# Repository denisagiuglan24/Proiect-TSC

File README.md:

# Proiect TSC - InkTime Smartwatch
**Student:** Giuglan Denisa-Cristina  
**Grupa:** 334CD  
---

## 1. Viziunea Proiectului si Arhitectura Sistemului

### Diagrama Bloc Hardware
Am structurat conexiunile pentru a separa magistrala rapida SPI (display) de magistrala senzorilor I2C, asigurand astfel o integritate maxima a semnalului.

```text
       ALIMENTARE (POWER)             SISTEM CENTRAL (MCU)                INTERFETE I/O
    _____________________          ___________________________          ____________________
   |                     |        |                           |        |                    |
   |   USB-C Connector   |---5V---|      nRF52840 (SoC)       |--SPI-->|   DISPLAY E-PAPER  |
   |_____________________|        |    Cortex-M4F @ 64MHz     |   Bus  |   (1.54" 24-pin)   |
              |                   |___________________________|        |____________________|
              v                    | P0.02 (SCK) | P0.03 (MOSI)
    _____________________          | P0.15 (DC)  | P0.16 (RST)          ____________________
   |                     |        |___________________________|        |                    |
   |   BQ25180 Charger   |--VBAT--|      MAGISTRALA I2C       |<------>|   ACCEL. BMA421    |
   |  (Li-Po Management) |        |      (SDA / SCL)          |   Bus  |   MAX17048 GAUGE   |
   |_____________________|        |___________________________|        |   DRV2605 HAPTIC   |
              ^                    | P0.26 (SDA) | P0.27 (SCL)         |____________________|
              |                    |___________________________|
    __________|__________          |                           |        ____________________
   |                     |         |   GPIO / PWM CONTROL      |       |                    |
   |   BATERIE LI-PO     |         |                           |------>|   MOTOR VIBRATII   |
   |      250 mAh        |         | P1.11 (PWM) | P0.13 (UP)  |       |____________________|
   |_____________________|         | P0.14 (ENT) | P1.02 (DN)  |<------|    3x BUTOANE      |
              |                    |___________________________|       |____________________|
              v                              |
    _____________________          __________|__________                ____________________
   |                     |        |                     |              |                    |
   |   RT6160A BUCK-B    |--3.3V--|   CRISTAL EXTERN    |------------->|      ANTENA RF     |
   |  (System Power)     |        |    (32.768 kHz)     |              |     (2.4 GHz)      |
   |_____________________|        |_____________________|              |____________________|
```
## 2. Documentatia Componentelor (BOM)

Am selectat componentele bazandu-ma pe catalogul **JLC Parts**, urmarind un raport optim intre dimensiune si performanta. Toate piesele pasive (rezistente/condensatoare) sunt in capsule **0201** si **0402**.

| Componenta | Package | Cod JLC Parts | Datasheet |
|:---|:---|:---|:---|
| **nRF52840-QIAA-R** (MCU) | aQFN73 | [C190794](https://jlcpcb.com/partdetail/Nordic_Semicon-NRF52840_QIAA_R/C190794) | [Link](https://docs.nordicsemi.com/) |
| **E-Paper Display 1.54"** | 24-pin FPC | [C359944](https://jlcpcb.com/partdetail/Waveshare-4_2inch_e_PaperModule/C359944) | [Link](https://www.waveshare.com/w/upload/e/e6/1.54inch_e-Paper_Datasheet.pdf) |
| **BQ25180YBGR** (Charger) | DSBGA-9 | [C3682423](https://jlcpcb.com/partdetail/TexasInstruments-BQ25180YBGR/C3682423) | [Link](https://www.ti.com/lit/ds/symlink/bq25180.pdf) |
| **RT6160AWSC** (Buck-Boost) | WLCSP-15 | [C7065276](https://jlcpcb.com/partdetail/Richtek_Tech-RT6160AWSC/C7065276) | [Link](https://www.richtek.com/assets/product_file/RT6160A/DS6160A-05.pdf) |
| **BMA421** (Accel) | LGA-12 | [C5242966](https://jlcpcb.com/partdetail/Bosch_Sensortec-BMA421/C5242966) | [Link](https://www.bosch-sensortec.com/media/boschsensortec/downloads/datasheets/bst-bma421-ds004.pdf) |
| **MAX17048G+T10** (Gauge) | DFN-8 | [C2682616](https://jlcpcb.com/partdetail/AnalogDevices-MAX17048G_T10/C2682616) | [Link](https://www.analog.com/media/en/technical-documentation/data-sheets/MAX17048-MAX17049.pdf) |
| **DRV2605YZFR** (Haptic) | VSSOP-10 | [C81079](https://jlcpcb.com/partdetail/TexasInstruments-DRV2605YZFR/C81079) | [Link](https://www.ti.com/lit/ds/symlink/drv2605.pdf) |
| **Antenna (2450AT18B100E)** | SMD 3216 | [C5179427](https://jlcpcb.com/partdetail/Johanson_Technology-2450AT18B100E/C5179427) | [Link](https://www.johansontechnology.com/datasheets/2450AT18B100/2450AT18B100.pdf) |
| **KH-TYPE-C-16P** (USB) | 16-pin SMD | [C2765186](https://jlcpcb.com/partdetail/Kinghelm-KH_TYPE_C_16P/C2765186) | [Link](https://datasheet.lcsc.com/lcsc/2012121836_Kinghelm-KH-TYPE-C-16P_C2765186.pdf) |
| **Molex 503480-2400** (FPC) | 24-pin SMD | [C2857168](https://jlcpcb.com/partdetail/Molex-5034802400/C2857160) | [Link](https://www.molex.com/en-us/products/part-detail/5034802400) |
| **USBLC6-2SC6Y** (ESD) | SOT-23-6 | [C7519](https://jlcpcb.com/partdetail/Stmicroelectronics-USBLC6_2SC6Y/C7519) | [Link](https://www.st.com/resource/en/datasheet/usblc6-2.pdf) |
| **Si2301CDS** (P-FET) | SOT-23 | [C10487](https://jlcpcb.com/partdetail/Vishay-Si2301CDS-T1-GE3/C10487) | [Link](https://www.vishay.com/docs/68749/si2301cds.pdf) |
| **EVP-AKB31A** (Butoane) | SMD Tactile | [C2845028](https://jlcpcb.com/partdetail/Panasonic-EVP_AKE31A/C2845028) | [Link](https://industrial.panasonic.com/cdbs/www-data/pdf/ATV0000/ATV0000CE3.pdf) |
| **Motor Vibratii** | Wire leads | [C7528006](https://jlcpcb.com/partdetail/7528806-LCM1027B3605F/C7528806) | [Link](https://datasheet.lcsc.com/lcsc/2310131633_LCM-LCM1027B3605F_C7528806.pdf) |
| **Crystal 32 MHz** | 2016 | [C5265841](https://jlcpcb.com/partdetail/Huiyuancrystal-HY32MSMD2016CA1R30/C5265841) | [Link](https://www.lcsc.com/product-detail/C7275071.html) |
| **Crystal 32.768 kHz** | 3215 | [C70509](https://jlcpcb.com/partdetail/NDK-NX3215SA_32_768KHZ_EXS00AMU00466/C70509) | [Link](https://www.ndk.com/images/products/catalog/c_NX3215SA_e.pdf) |
| **Inductor 0.47uH** | 2016 | [C5832368](https://jlcpcb.com/partdetail/6763488-FTC252012SR47MBCA/C5832368) | [Link](https://www.lcsc.com/product-detail/C5832368.html) |
| **Inductor 10uH** | 0402 | [C910650](https://jlcpcb.com/partdetail/MurataElectronics-LQW15DN100M00D/C910650) | [Link](https://www.murata.com/en-us/products/productdetail?partno=LQW15DN100M00%23) |
| **Rezistenta 10k Ω** | 0201 | [C100126](https://jlcpcb.com/partdetail/LIZElec-CR0201FH1002G/C100126) | [Link](https://www.lcsc.com/product-detail/C100126.html) |
| **Rezistenta 5.1k Ω** | 0201 | [C100142](https://jlcpcb.com/partdetail/LIZElec-CR0201FH5101G/C100142) | [Link](https://www.lcsc.com/product-detail/C5266011.html) |
| **Condensator 1uF** | 0402 | [C14445](https://jlcpcb.com/partdetail/15107-CL05A105KP5NNNC/C14445) | [Link](https://weblib.samsungsem.com/) |
| **Condensator 100nF** | 0201 | [C49062](https://jlcpcb.com/partdetail/50070-CL03A104KP3NNNC/C49062) | [Link](https://www.lcsc.com/product-detail/C49062.html) |
| **Condensator 4.7uF** | 0402 | [C23687](https://jlcpcb.com/partdetail/TDK-C1005X5R0J475MTJ00E/C23687) | [Link](https://www.lcsc.com/product-detail/C23687.html) |
| **Condensator 22uF** | 0402 | [C105226](https://jlcpcb.com/partdetail/106441-CL05A226MQ5QUNC/C105226) | [Link](https://www.lcsc.com/product-detail/C105226.html) |
| **Condensator 12pF** | 0201 | [C50391](https://jlcpcb.com/partdetail/51400-0201CG120J500NT/C50391) | [Link](https://www.lcsc.com/product-detail/C50391.html) |
| **LiPo 250mAh** | Baterie | - | [Link](https://www.tme.eu/Document/b9e12bf26ad0ba929a22ab5d58f022cd/AKY0106.pdf) |
| **TC2030-IDC** (Debug) | Footprint | - | [Link](https://www.tag-connect.com/product/tc2030-idc) |

---

## 3. Analiza Functionalitatii Hardware

In aceasta faza a proiectului, m-am concentrat pe implementarea unui sistem care sa poata functiona independent de o sursa de curent externa pentru perioade lungi.

### 3.1 Unitatea Centrala si Conectivitatea
Am optat pentru **nRF52840** datorita arhitecturii sale flexibile. Acesta imi permite sa folosesc USB-ul nativ pentru debug si transfer de date, in timp ce interfata radio BLE asigura sincronizarea cu telefonul. Pentru a asigura o precizie ridicata a timpului, am adaugat un cristal extern de **32.768 kHz**, esential pentru ca ceasul sa nu piarda secunde in modurile sleep.

### 3.2 Sistemul de Afisaj E-Paper
In loc de un ecran clasic care necesita iluminare constanta, am integrat un display E-Paper de 1.54 inch. Acesta utilizeaza particule incarcate electric care isi pastreaza pozitia fara consum de energie. Am conectat ecranul prin **SPI**, trimitand datele la frecventa maxima suportata pentru a finaliza refresh-ul rapid si a permite procesorului sa intre inapoi in starea de consum minim.

### 3.3 Managementul Energiei
Alimentarea este asigurata de o baterie Li-Po de 250mAh. Am integrat un circuit **Buck-Boost RT6160A** pentru a ma asigura ca, indiferent de nivelul de descarcare al bateriei (intre 4.2V si 3.0V), sistemul primeste un 3.3V stabil. Incarcarea este gestionata inteligent de **BQ25180**, iar monitorizarea procentului bateriei se face prin **MAX17048**, care raporteaza datele catre MCU prin magistrala I2C.

---

## 4. Alocarea Pinilor nRF52840 (Justificare Tehnica)

In procesul de layout, am ales pinii pentru a optimiza rutarea si a separa semnalele de mare viteza de cele de control.

| Pin nRF | Conectat la | Ratiune Tehnica / Explicatie |
|:---|:---|:---|
| **P0.02** | E-Paper SCK | Pin de clock SPI de mare viteza, ales pentru capabilitatea High-Drive. |
| **P0.03** | E-Paper MOSI | Linie de date SPI catre display, plasata langa clock pentru a asigura integritatea semnalului. |
| **P0.15** | E-Paper DC | Data/Command select, esential pentru protocolul controller-ului EPD. |
| **P0.26** | I2C SDA | Linie de date pentru magistrala comuna (IMU, Fuel Gauge, Haptic). |
| **P0.27** | I2C SCL | Semnal de ceas pentru magistrala I2C. |
| **P1.11** | PWM Haptic | Controlul motorului de vibratii, plasat pe Portul 1 pentru a izola zgomotul de comutatie. |
| **P0.13** | Button UP | Intrare GPIO cu rezistenta pull-up interna; poate trezi MCU din sleep (SENSE). |
| **P0.14** | Button ENTER| Intrare digitala pentru selectie si confirmare in meniu. |
| **P1.02** | Button DOWN | Navigare interfata utilizator. |
| **SWDIO / SWDCLK**| Debug/Prog | Interfata Serial Wire Debug folosita pentru programare prin header-ul Tag-Connect. |

---

## 5. Estimarea Consumului si Autonomia

Am proiectat InkTime cu un consum in "Deep Sleep" (System ON) estimat la **~84 uA** (MCU sleep, RTC activ, senzori in low-power).
* In timpul unui **refresh de ecran**, avem un varf de consum de pana la **15 mA** pentru o durata scurta.
* In modul **standby**, tehnologia E-Ink consuma **0 mA** pentru a mentine imaginea.

**Calcul Autonomie:** Cu o baterie de 250 mAh, la un regim de utilizare mediu (refresh ceas o data pe minut si notificari BLE), autonomia estimata este de **~30 de zile**, oferind o experienta superioara smartwatch-urilor clasice.

---

## 6. Design Mecanic si Integrare 3D

Integrarea componentelor a fost realizata in **Fusion 360**, adoptand o structura compacta de tip sandwich:
* **Carcasa Superioara:** Protejeaza display-ul si asigura etanseitatea.
* **PCB:** Placa de 2 straturi pe care sunt montate toate componentele SMD.
* **Carcasa Inferioara:** Gazduieste bateria Li-Po si motorul haptic, fiind fixata prin presare si suruburi de precizie.
Am generat fisierele **.step** pentru vederea explodata si **.f3z** pentru proiectul sursa, asigurand compatibilitatea cu procesele de fabricatie.

---

## 📂 Organizare Repository
* **/Hardware**: Schema electronica (.sch) si design PCB (.brd).
* **/Manufacturing**: Arhiva Gerber, fisiere BOM si Pick&Place.
* **/Mechanical**: Modele CAD 3D (.step, .f3z).
* **/Images**: Randari si capturi de ecran.

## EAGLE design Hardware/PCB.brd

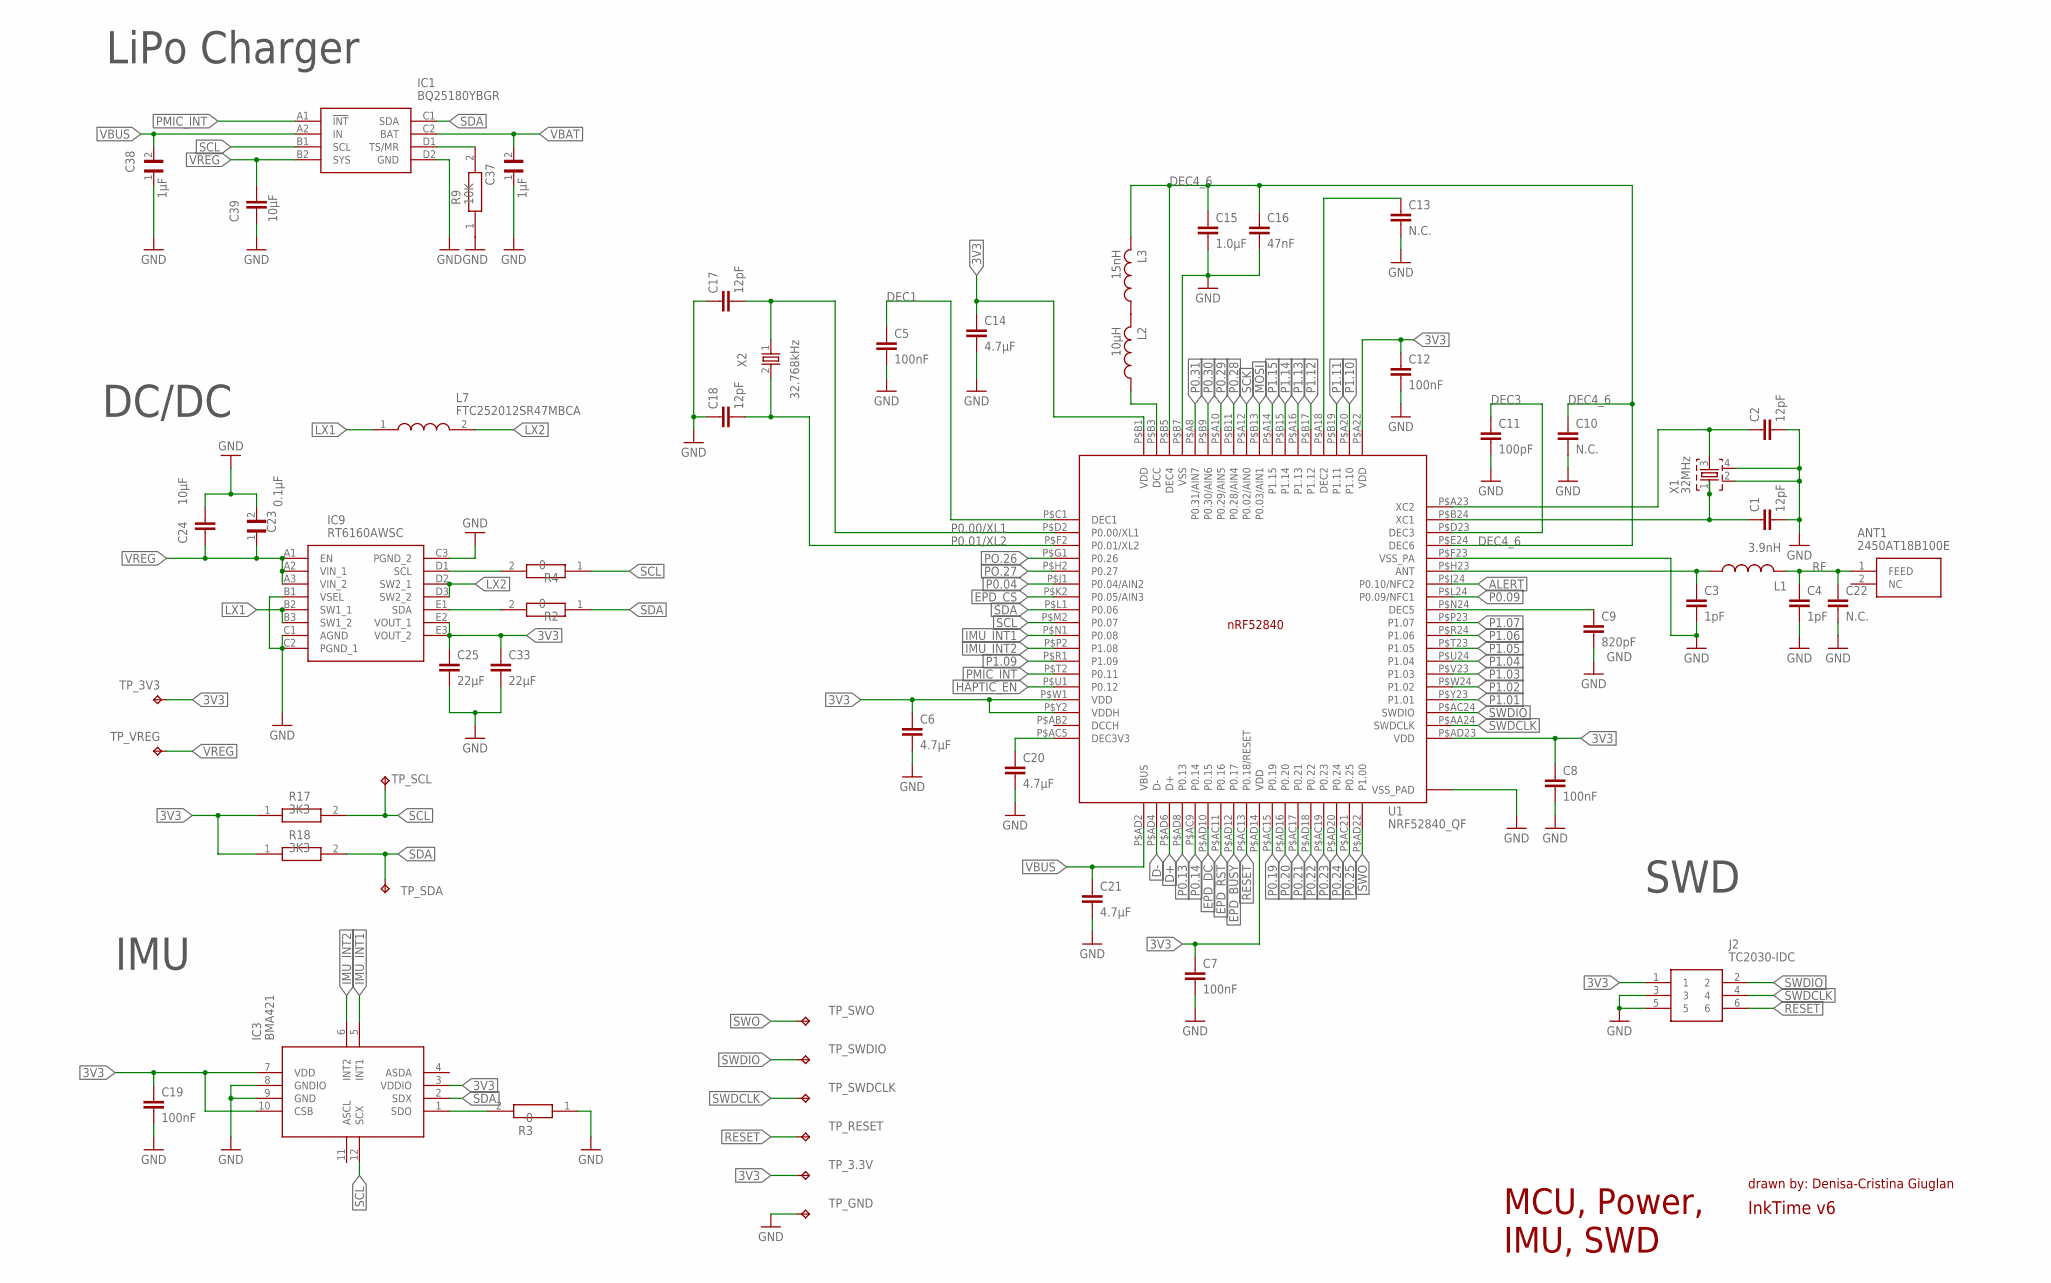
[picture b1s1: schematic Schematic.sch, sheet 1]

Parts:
ANT1: 2450AT18B100E; 2450AT18B100E_ANTC3216X140N
C1, C2, C17, C18: 12pF; NORDIC_NRF_3_RESC0201_L
C3: 1pF; NORDIC_NRF_3_RESC0402_N
C4: 1pF; NORDIC_NRF_3_RESC0201_L
C5, C7, C8, C12, C19: 100nF; NORDIC_NRF_3_RESC0201_L
C6, C14, C20, C21: 4.7μF; NORDIC_NRF_3_RESC0402_N
C9: 820pF; NORDIC_NRF_3_RESC0201_L
C10, C13, C22: N.C.; NORDIC_NRF_3_RESC0402_N
C11: 100pF; NORDIC_NRF_3_RESC0402_N
C15: 1.0μF; NORDIC_NRF_3_RESC0402_N
C16: 47nF; NORDIC_NRF_3_RESC0201_L
C23: 0.1μF; GRM011R60J152KE01L_2_CAPC0201X13N
C24, C39: 10μF; NORDIC_NRF_3_RESC0402_N
C25, C33: 22μF; NORDIC_NRF_3_RESC0402_N
C37, C38: 1μF; GRM011R60J152KE01L_2_CAPC0201X13N
IC1: BQ25180YBGR; BQ25180YBGR_BGA8C40P2X4_100X155X50
IC3: BMA421; BMA423_BMA423
IC9: RT6160AWSC; RT6160AWSC_BGA15C40P3X5_140X230X60
J2: TC2030-IDC; TC2030-IDC_TC2030IDC
L1: 3.9nH; NORDIC_NRF_2_RESC0402_L
L2: 10μH; NORDIC_NRF_2_RESC0402_L
L3: 15nH; NORDIC_NRF_2_RESC0402_L
L7: FTC252012SR47MBCA; MLP2016SR47MT0S1_INDC2016X100N
R2, R3, R4: 0; CPF0201D7K68C1_0201
R9: 10K; CPF0201D7K68C1_0201
R17, R18: 3K3; CPF0201D7K68C1_0201
TP_3.3V, TP_3V3: HECTOR_WATCH_1_TPTP20R; HECTOR_WATCH_1_TP20R
TP_GND: HECTOR_WATCH_1_TPTP20R; HECTOR_WATCH_1_TP20R
TP_RESET: HECTOR_WATCH_1_TPTP20R; HECTOR_WATCH_1_TP20R
TP_SCL: HECTOR_WATCH_1_TPTP20R; HECTOR_WATCH_1_TP20R
TP_SDA: HECTOR_WATCH_1_TPTP20R; HECTOR_WATCH_1_TP20R
TP_SWDCLK: HECTOR_WATCH_1_TPTP20R; HECTOR_WATCH_1_TP20R
TP_SWDIO: HECTOR_WATCH_1_TPTP20R; HECTOR_WATCH_1_TP20R
TP_SWO: HECTOR_WATCH_1_TPTP20R; HECTOR_WATCH_1_TP20R
TP_VREG: HECTOR_WATCH_1_TPTP20R; HECTOR_WATCH_1_TP20R
U1: NRF52840_QF; NORDIC_NRF_4_AQFN50P700X700X85_HS-74N
X1: 32MHz; NORDIC_NRF_BT-XTAL_2016_N
X2: 32.768kHz; NORDIC_NRF_1_XTAL_3215_N

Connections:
3V3: C6.1, C7.1, C8.1, C12.1, C14.1, C19.1, C25.1, C33.1, IC3.3 (VDDIO), IC3.7 (VDD), IC3.10 (CSB), IC9.E2 (VOUT_1), IC9.E3 (VOUT_2), J2.1, R17.1, R18.1, TP_3.3V.TP, TP_3V3.TP, U1.P$A22 (VDD), U1.P$AD14 (VDD), U1.P$AD23 (VDD), U1.P$B1 (VDD), U1.P$W1 (VDD), U1.P$Y2 (VDDH); also elsewhere on the board
ALERT: U1.P$J24 (P0.10/NFC2); also elsewhere on the board
D+: U1.P$AD6 (D+); also elsewhere on the board
D-: U1.P$AD4 (D-); also elsewhere on the board
DEC1: C5.1, U1.P$C1 (DEC1)
DEC3: C11.1, U1.P$D23 (DEC3)
DEC4_6: C10.1, C15.1, C16.1, L3.2, U1.P$B5 (DEC4), U1.P$E24 (DEC6)
EPD_BUSY: U1.P$AD12 (P0.17); also elsewhere on the board
EPD_CS: U1.P$K2 (P0.05/AIN3); also elsewhere on the board
EPD_DC: U1.P$AD10 (P0.15); also elsewhere on the board
EPD_RST: U1.P$AC11 (P0.16); also elsewhere on the board
GND: C1.2, C2.2, C3.2, C4.2, C5.2, C6.2, C7.2, C8.2, C9.2, C10.2, C11.2, C12.2, C13.2, C14.2, C15.2, C16.2, C17.1, C18.1, C19.2, C20.2, C21.2, C22.2, C23.2, C24.1, C25.2, C33.2, C37.1, C38.1, C39.2, IC1.D2 (GND), IC3.8 (GNDIO), IC3.9 (GND), IC9.B1 (VSEL), IC9.C1 (AGND), IC9.C2 (PGND_1), IC9.C3 (PGND_2), J2.3, J2.5, R3.1, R9.1, TP_GND.TP, U1.P$74 (VSS_PAD), U1.P$75 (VSS_PAD), U1.P$76 (VSS_PAD), U1.P$77 (VSS_PAD), U1.P$78 (VSS_PAD), U1.P$79 (VSS_PAD), U1.P$80 (VSS_PAD), U1.P$81 (VSS_PAD), U1.P$82 (VSS_PAD), U1.P$83 (VSS_PAD), U1.P$84 (VSS_PAD), U1.P$85 (VSS_PAD), U1.P$86 (VSS_PAD), U1.P$87 (VSS_PAD), U1.P$88 (VSS_PAD), U1.P$89 (VSS_PAD), U1.P$90 (VSS_PAD), U1.P$B7 (VSS), U1.P$F23 (VSS_PA), X1.2, X1.4; also elsewhere on the board
HAPTIC_EN: U1.P$U1 (P0.12); also elsewhere on the board
IMU_INT1: IC3.5 (INT1), U1.P$N1 (P0.08)
IMU_INT2: IC3.6 (INT2), U1.P$P2 (P1.08)
LX1: IC9.B2 (SW1_1), IC9.B3 (SW1_2), L7.1
LX2: IC9.D2 (SW2_1), IC9.D3 (SW2_2), L7.2
MOSI: U1.P$B13 (P0.03/AIN1); also elsewhere on the board
unnamed: IC9.D1 (SCL), R4.2
unnamed: C20.1, U1.P$AC5 (DEC3V3)
unnamed: IC9.E1 (SDA), R2.2
unnamed: L2.1, U1.P$B3 (DCC)
unnamed: IC1.D1 (TS/MR), R9.2
unnamed: IC3.1 (SDO), R3.2
unnamed: L2.2, L3.1
unnamed: C13.1, U1.P$A18 (DEC2)
unnamed: C9.1, U1.P$N24 (DEC5)
unnamed: C3.1, L1.1, U1.P$H23 (ANT)
unnamed: C2.1, U1.P$A23 (XC2), X1.3
unnamed: C1.1, U1.P$B24 (XC1), X1.1
P0.00/XL1: C17.2, U1.P$D2 (P0.00/XL1), X2.1
P0.01/XL2: C18.2, U1.P$F2 (P0.01/XL2), X2.2
P0.04: U1.P$J1 (P0.04/AIN2)
P0.09: U1.P$L24 (P0.09/NFC1)
P0.13: U1.P$AD8 (P0.13); also elsewhere on the board
P0.14: U1.P$AC9 (P0.14); also elsewhere on the board
P0.19: U1.P$AC15 (P0.19)
P0.20: U1.P$AD16 (P0.20)
P0.21: U1.P$AC17 (P0.21)
P0.22: U1.P$AD18 (P0.22)
P0.23: U1.P$AC19 (P0.23)
P0.24: U1.P$AD20 (P0.24)
P0.25: U1.P$AC21 (P0.25)
P0.28: U1.P$B11 (P0.28/AIN4)
P0.29: U1.P$A10 (P0.29/AIN5)
P0.30: U1.P$B9 (P0.30/AIN6)
P0.31: U1.P$A8 (P0.31/AIN7)
P1.01: U1.P$Y23 (P1.01); also elsewhere on the board
P1.02: U1.P$W24 (P1.02); also elsewhere on the board
P1.03: U1.P$V23 (P1.03)
P1.04: U1.P$U24 (P1.04)
P1.05: U1.P$T23 (P1.05)
P1.06: U1.P$R24 (P1.06)
P1.07: U1.P$P23 (P1.07)
P1.09: U1.P$R1 (P1.09)
P1.10: U1.P$A20 (P1.10)
P1.11: U1.P$B19 (P1.11)
P1.12: U1.P$B17 (P1.12)
P1.13: U1.P$A16 (P1.13)
P1.14: U1.P$B15 (P1.14)
P1.15: U1.P$A14 (P1.15)
PMIC_INT: IC1.A1 (!INT), U1.P$T2 (P0.11)
PO.26: U1.P$G1 (P0.26)
PO.27: U1.P$H2 (P0.27)
RESET: J2.6, TP_RESET.TP, U1.P$AC13 (P0.18/RESET)
RF: ANT1.1 (FEED), C4.1, C22.1, L1.2
SCK: U1.P$A12 (P0.02/AIN0); also elsewhere on the board
SCL: IC1.B1 (SCL), IC3.12 (SCX), R4.1, R17.2, TP_SCL.TP, U1.P$M2 (P0.07); also elsewhere on the board
SDA: IC1.C1 (SDA), IC3.2 (SDX), R2.1, R18.2, TP_SDA.TP, U1.P$L1 (P0.06); also elsewhere on the board
SWDCLK: J2.4, TP_SWDCLK.TP, U1.P$AA24 (SWDCLK)
SWDIO: J2.2, TP_SWDIO.TP, U1.P$AC24 (SWDIO)
SWO: TP_SWO.TP, U1.P$AD22 (P1.00)
VBAT: C37.2, IC1.C2 (BAT); also elsewhere on the board
VBUS: C21.1, C38.2, IC1.A2 (IN), U1.P$AD2 (VBUS); also elsewhere on the board
VREG: C23.1, C24.2, C39.1, IC1.B2 (SYS), IC9.A1 (EN), IC9.A2 (VIN_1), IC9.A3 (VIN_2), TP_VREG.TP

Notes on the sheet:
LiPo Charger
DC/DC
IMU
SWD
MCU, Power, IMU, SWD
InkTime v6
drawn by: Denisa-Cristina Giuglan

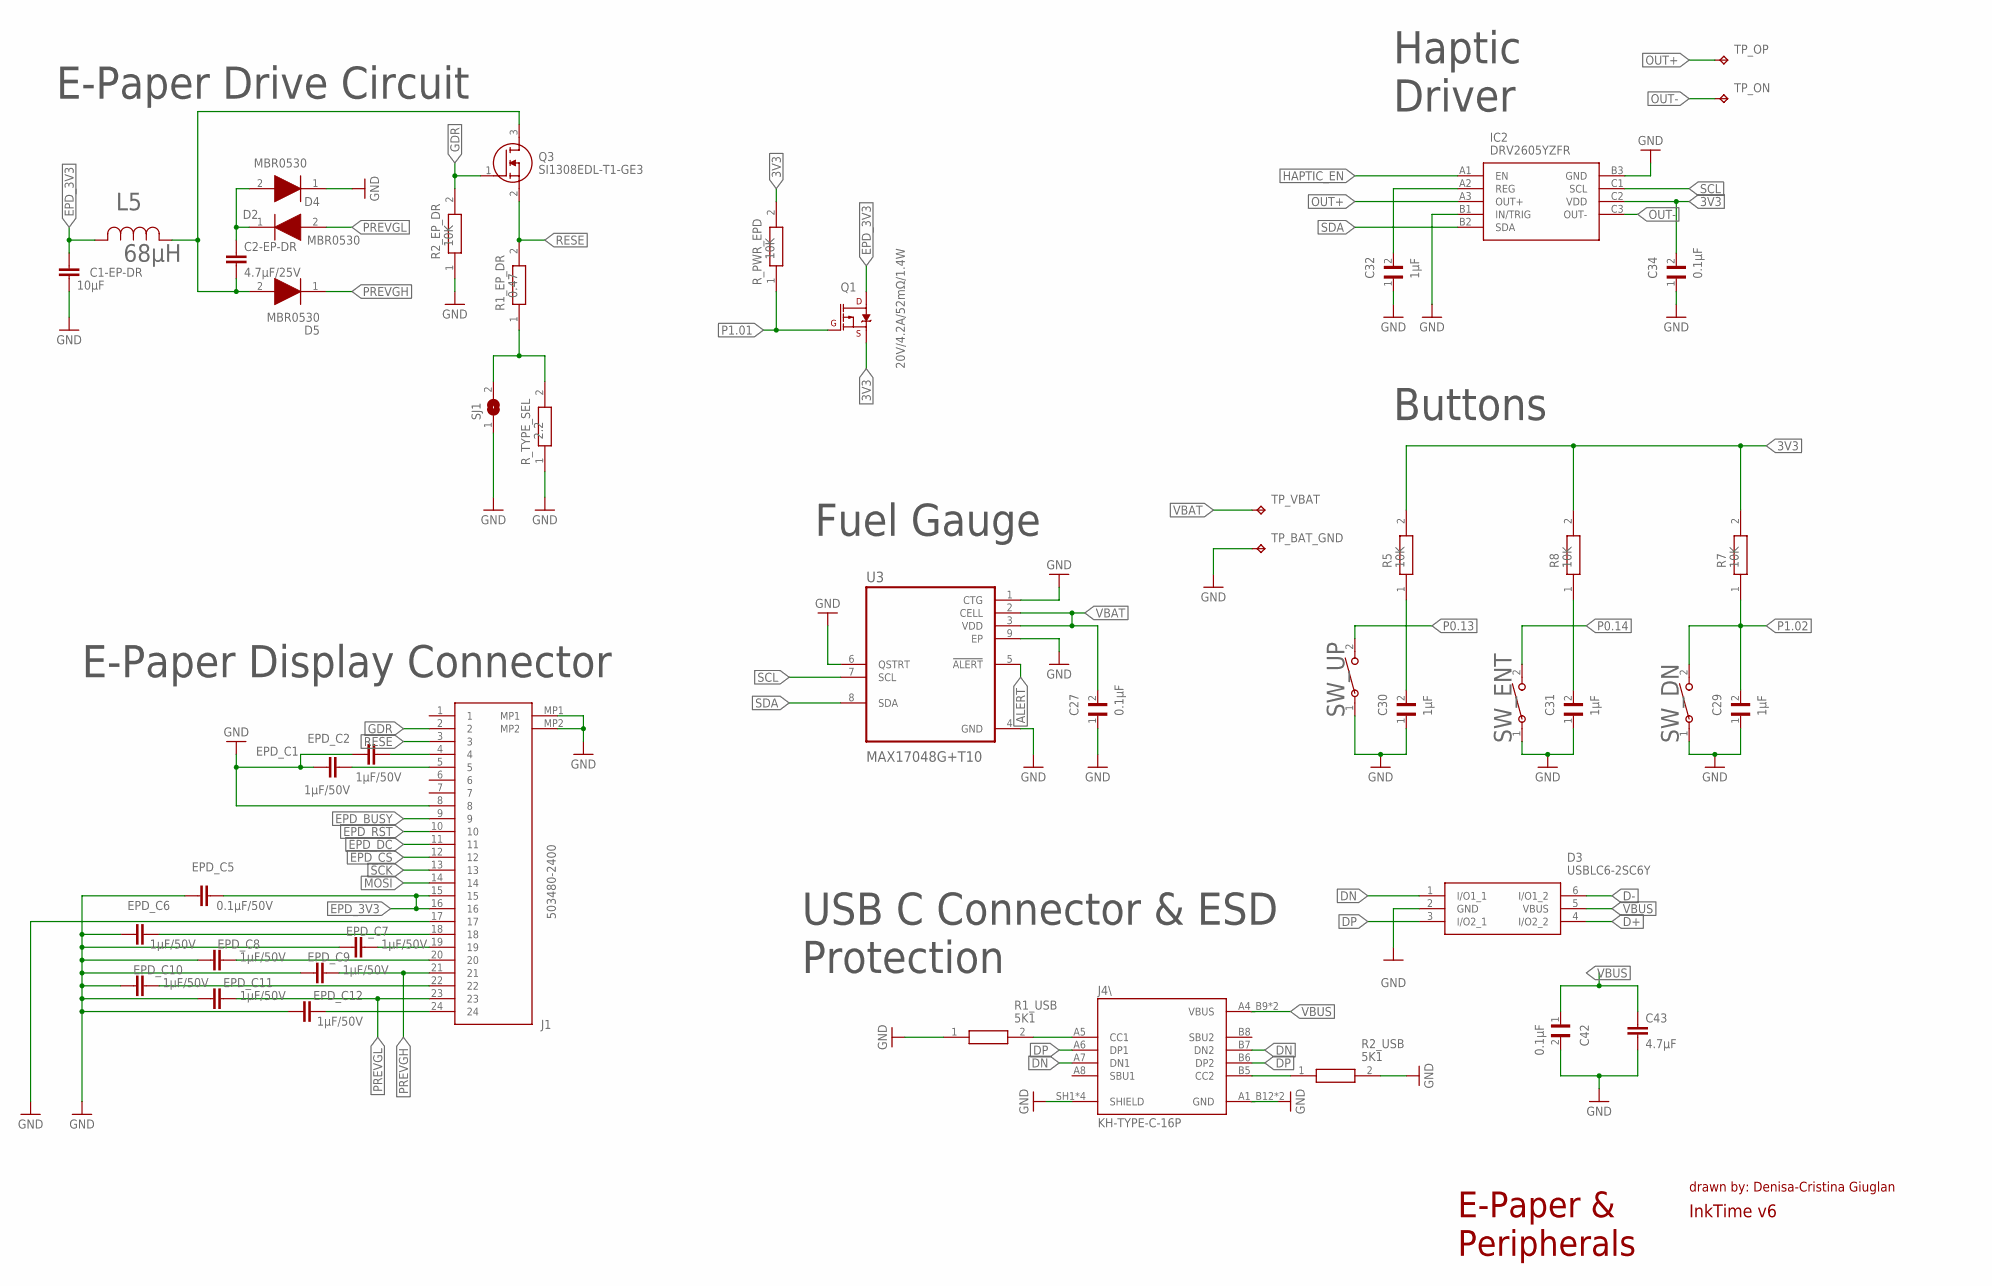
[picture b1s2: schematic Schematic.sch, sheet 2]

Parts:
C1-EP-DR: 10μF; NORDIC_NRF_3_RESC0402_N
C2-EP-DR: 4.7μF/25V; NORDIC_NRF_3_RESC0402_N
C27, C34, C42: 0.1μF; GRM011R60J152KE01L_2_CAPC0201X13N
C29, C30, C31, C32: 1μF; GRM011R60J152KE01L_2_CAPC0201X13N
C43: 4.7μF; NORDIC_NRF_3_RESC0402_N
D2, D4, D5: MBR0530; ESP32_C6_LIBRARY_5_SOD3716X135N
D3: USBLC6-2SC6Y; ESP32_C6_LIBRARY_3_SOT95P280X145-6N
EPD_C1, EPD_C2, EPD_C6, EPD_C7, EPD_C8, EPD_C9, EPD_C10, EPD_C11, EPD_C12: 1μF/50V; NORDIC_NRF_3_RESC0402_N
EPD_C5: 0.1μF/50V; NORDIC_NRF_3_RESC0402_N
IC2: DRV2605YZFR; DRV2605YZFR_BGA9C50P3X3_144X144X62
J1: 503480-2400; 503480-2400_5034802400
J4\: KH-TYPE-C-16P; KH-TYPE-C-16P_KINGHELM_KH-TYPE-C-16P
L5: 68μH; ESP32_C6_LIBRARY_2_IND_4828-WE-TPC_WRE
Q1: 20V/4.2A/52mΩ/1.4W; ESP32_C6_LIBRARY_4_ESP32_C6_LIBRARY_4_ESP32_C6_LIBRARY_4_ES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
Q3: SI1308EDL-T1-GE3; ESP32_C6_LIBRARY_6_SOT65P210X110-3N
R1_EP_DR: 0.47; CPF0201D7K68C1_0201
R1_USB, R2_USB: 5K1; CPF0201D7K68C1_0201
R2_EP_DR, R5, R7, R8: 10K; CPF0201D7K68C1_0201
R_PWR_EPD: 10K; CPF0201D7K68C1_0201
R_TYPE_SEL: 2.2; CPF0201D7K68C1_0201
SJ1: ESP32_C6_LIBRARY_7_JUMPER_SJ
SW_DN: 2025-10-22_07-23-44_LIBRARY_EVP-AKE31ASW_EVP-AKE3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; 2025-10-22_07-23-44_LIBRARY_SW_EVP-AKE31A_PAN
SW_ENT: 2025-10-22_07-23-44_LIBRARY_EVP-AKE31ASW_EVP-AKE3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; 2025-10-22_07-23-44_LIBRARY_SW_EVP-AKE31A_PAN
SW_UP: 2025-10-22_07-23-44_LIBRARY_EVP-AKE31ASW_EVP-AKE3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; 2025-10-22_07-23-44_LIBRARY_SW_EVP-AKE31A_PAN
TP_BAT_GND: HECTOR_WATCH_1_TPTP20R; HECTOR_WATCH_1_TP20R
TP_ON: HECTOR_WATCH_1_TPTP20R; HECTOR_WATCH_1_TP20R
TP_OP: HECTOR_WATCH_1_TPTP20R; HECTOR_WATCH_1_TP20R
TP_VBAT: HECTOR_WATCH_1_TPTP20R; HECTOR_WATCH_1_TP20R
U3: MAX17048G+T10; ESP32_C6_LIBRARY_SON50P200X200X80-9N

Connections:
3V3: C34.2, IC2.C2 (VDD), Q1.2 (S), R5.2, R7.2, R8.2, R_PWR_EPD.2; also elsewhere on the board
ALERT: U3.5 (!ALERT); also elsewhere on the board
D+: D3.4 (I/O2_2); also elsewhere on the board
D-: D3.6 (I/O1_2); also elsewhere on the board
DN: D3.1 (I/O1_1), J4\.A7 (DN1), J4\.B7 (DN2)
DP: D3.3 (I/O2_1), J4\.A6 (DP1), J4\.B6 (DP2)
EPD_3V3: C1-EP-DR.1, EPD_C5.2, J1.15, J1.16, L5.2, Q1.3 (D)
EPD_BUSY: J1.9; also elsewhere on the board
EPD_CS: J1.12; also elsewhere on the board
EPD_DC: J1.11; also elsewhere on the board
EPD_RST: J1.10; also elsewhere on the board
GDR: J1.2, Q3.1 (G), R2_EP_DR.2
GND: C1-EP-DR.2, C27.1, C29.1, C30.1, C31.1, C32.1, C34.1, C42.2, C43.2, D3.2 (GND), D4.1 (K), EPD_C1.1, EPD_C2.1, EPD_C5.1, EPD_C6.1, EPD_C7.1, EPD_C8.1, EPD_C9.1, EPD_C10.1, EPD_C11.1, EPD_C12.1, IC2.B1 (IN/TRIG), IC2.B3 (GND), J1.8, J1.17, J1.MP1, J1.MP2, J4\.A1_B12 (GND), J4\.A12_B1 (GND), J4\.SH1 (SHIELD), J4\.SH2 (SHIELD), J4\.SH3 (SHIELD), J4\.SH4 (SHIELD), R1_USB.1, R2_EP_DR.1, R2_USB.2, R_TYPE_SEL.1, SJ1.1, SW_DN.1, SW_ENT.1, SW_UP.1, TP_BAT_GND.TP, U3.1 (CTG), U3.4 (GND), U3.6 (QSTRT), U3.9 (EP); also elsewhere on the board
HAPTIC_EN: IC2.A1 (EN); also elsewhere on the board
MOSI: J1.14; also elsewhere on the board
unnamed: J4\.A5 (CC1), R1_USB.2
unnamed: EPD_C2.2, J1.4
unnamed: EPD_C1.2, J1.5
unnamed: J4\.B5 (CC2), R2_USB.1
unnamed: C31.2, R8.1
unnamed: C2-EP-DR.1, D2.1 (K), D4.2 (A)
unnamed: C30.2, R5.1
unnamed: C2-EP-DR.2, D5.2 (A), L5.1, Q3.3 (D)
unnamed: EPD_C6.2, J1.18
unnamed: C32.2, IC2.A2 (REG)
unnamed: EPD_C7.2, J1.19
unnamed: EPD_C8.2, J1.20
unnamed: EPD_C10.2, J1.22
unnamed: EPD_C12.2, J1.24
unnamed: R1_EP_DR.1, R_TYPE_SEL.2, SJ1.2
OUT+: IC2.A3 (OUT+), TP_OP.TP
OUT-: IC2.C3 (OUT-), TP_ON.TP
P0.13: SW_UP.2; also elsewhere on the board
P0.14: SW_ENT.2; also elsewhere on the board
P1.01: Q1.1 (G), R_PWR_EPD.1; also elsewhere on the board
P1.02: C29.2, R7.1, SW_DN.2; also elsewhere on the board
PREVGH: D5.1 (K), EPD_C9.2, J1.21
PREVGL: D2.2 (A), EPD_C11.2, J1.23
RESE: J1.3, Q3.2 (S), R1_EP_DR.2
SCK: J1.13; also elsewhere on the board
SCL: IC2.C1 (SCL), U3.7 (SCL); also elsewhere on the board
SDA: IC2.B2 (SDA), U3.8 (SDA); also elsewhere on the board
VBAT: C27.2, TP_VBAT.TP, U3.2 (CELL), U3.3 (VDD); also elsewhere on the board
VBUS: C42.1, C43.1, D3.5 (VBUS), J4\.A4_B9 (VBUS), J4\.A9_B4 (VBUS); also elsewhere on the board

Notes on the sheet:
E-Paper Drive Circuit
E-Paper Display Connector
Haptic Driver
Buttons
Fuel Gauge
USB C Connector & ESD Protection
E-Paper & Peripherals
InkTime v6
drawn by: Denisa-Cristina Giuglan

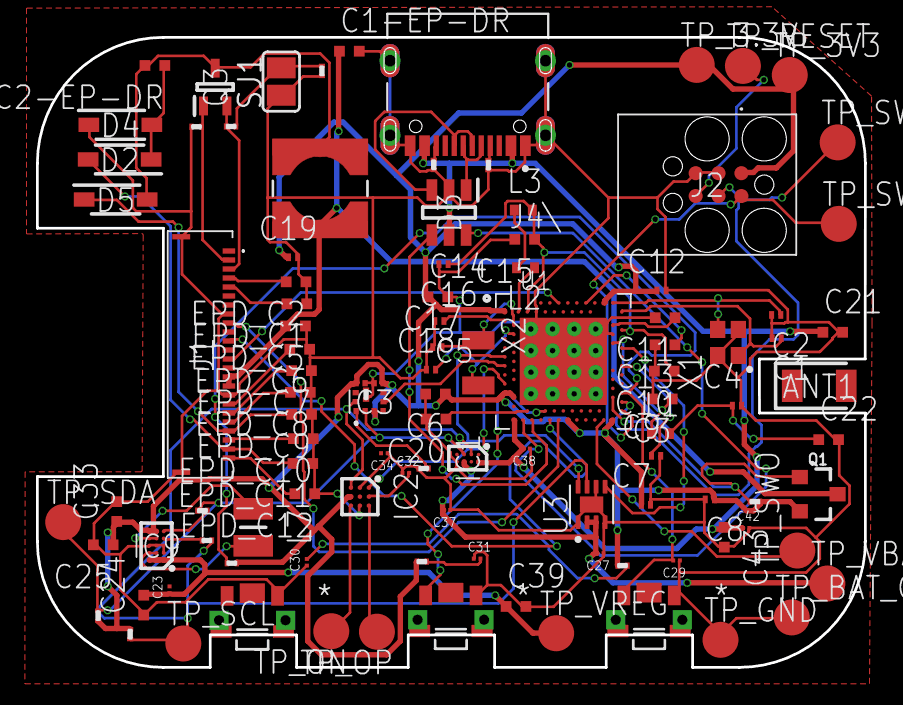
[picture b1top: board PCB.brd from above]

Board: 2 copper layers, 46.0 x 35.0 mm, 105 parts (0 on the bottom side), 72 nets.

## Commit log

2026-04-10 Schematic+PCB
2026-04-10 Added images and manufacturing
2026-04-10 Added mechanical
2026-04-22 Added gerbers.zip

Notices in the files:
parts and their libraries:
COPYRIGHT: Copyright (C) 2024 Ultra Librarian. All rights reserved.
COPYRIGHT: Copyright (C) 2025 Ultra Librarian. All rights reserved.
